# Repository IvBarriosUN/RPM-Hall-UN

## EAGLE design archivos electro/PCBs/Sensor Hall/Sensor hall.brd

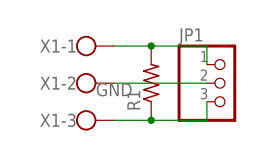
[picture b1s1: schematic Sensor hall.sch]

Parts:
JP1: PINHD-1X3; 1X03
R1: R-US_0411/15; 0411/15
X1: W237-103

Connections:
GND: JP1.2, X1.2
unnamed: JP1.1, R1.2, X1.1
unnamed: JP1.3, R1.1, X1.3

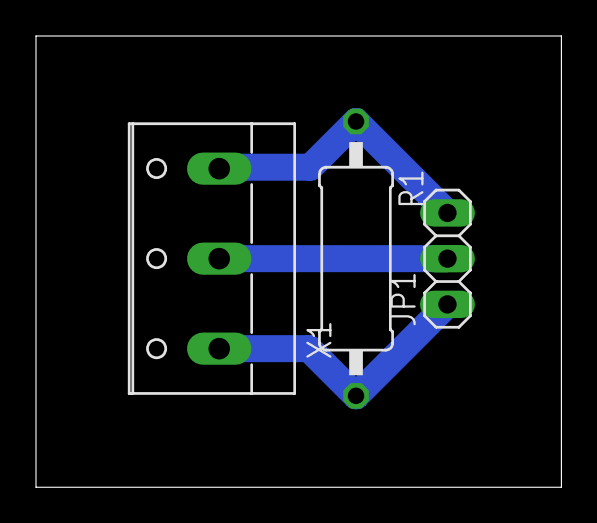
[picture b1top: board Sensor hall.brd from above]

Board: 2 copper layers, 29.2 x 25.1 mm, 3 parts (0 on the bottom side), 3 nets.

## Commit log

2025-06-05 Create Cuaderno
